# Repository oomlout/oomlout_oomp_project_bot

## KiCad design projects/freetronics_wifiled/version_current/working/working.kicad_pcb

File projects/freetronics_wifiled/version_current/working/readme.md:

# WIFILED by freetronics  
This is a harvested standardized copy of a project from github.  
The original project can be found at:  
https://github.com/freetronics/WIFILED  
Please consult that link for additional, details, files, and license information.  
Note: It was auto harvested and if the original repo had more than one board file or anything out of the ordinary the files here are likely not representative.

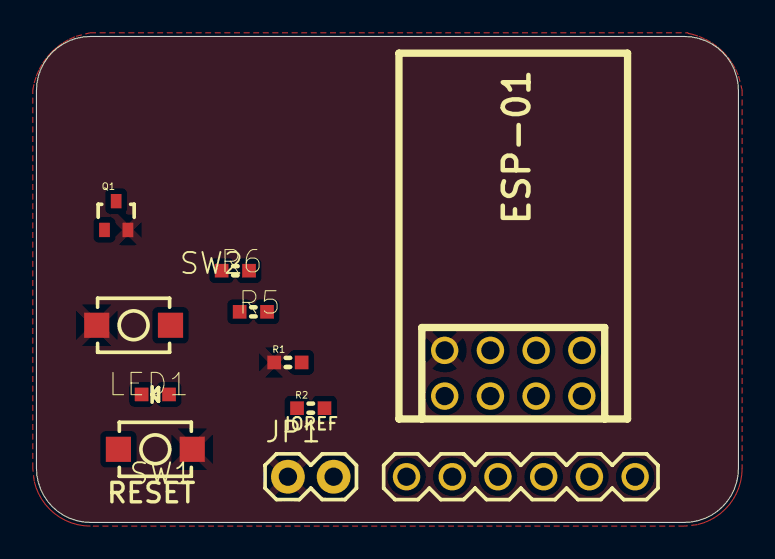
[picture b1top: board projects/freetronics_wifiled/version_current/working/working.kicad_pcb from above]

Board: 2 copper layers, 39.0 x 27.0 mm, 11 parts (0 on the bottom side), 9 nets, no tracks yet.

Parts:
J2: FTDI; 1X06
J9: ESP01
JP1: 1X02
LED1: BLUE; LED-0603
Q1: 2N7002 SOT-323; SOT32-3
R1, R6: 22K; 0603
R2, R5: 1K; 0603
SW1: RESET; TACTILE_SWITCH_SMD_2PIN_TINY
SW2: REFLASH; TACTILE_SWITCH_SMD_2PIN_TINY

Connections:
3.3V: J9.4, JP1.2, R5.2, R6.2
GND: J9.8, JP1.1, Q1.2, R1.1, SW1.1, SW2.2
unnamed: J9.6, SW2.1
unnamed: LED1.C, Q1.3
unnamed: J9.3, SW1.2
unnamed: J9.2, R6.1
unnamed: LED1.A, R5.1
unnamed: Q1.1, R1.2, R2.2
TX: J9.1, R2.1

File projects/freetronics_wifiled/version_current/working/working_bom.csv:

"Id";"Designator";"Footprint";"Quantity";"Designation";"Supplier and ref";
1;"R1,R6";"0603";2;"22K";;;
2;"SW2";"TACTILE_SWITCH_SMD_2PIN_TINY";1;"REFLASH";;;
3;"LED1";"LED-0603";1;"BLUE";;;
4;"J9";"ESP01";1;"ESP01";;;
5;"R2,R5";"0603";2;"1K";;;
6;"J2";"1X06";1;"FTDI";;;
7;"SW1";"TACTILE_SWITCH_SMD_2PIN_TINY";1;"RESET";;;
8;"Q1";"SOT32-3";1;"2N7002 SOT-323";;;
9;"JP1";"1X02";1;"";;;

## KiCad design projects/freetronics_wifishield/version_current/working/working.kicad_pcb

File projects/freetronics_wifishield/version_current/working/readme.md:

# WiFiShield by freetronics  
This is a harvested standardized copy of a project from github.  
The original project can be found at:  
https://github.com/freetronics/WiFiShield  
Please consult that link for additional, details, files, and license information.  
Note: It was auto harvested and if the original repo had more than one board file or anything out of the ordinary the files here are likely not representative.

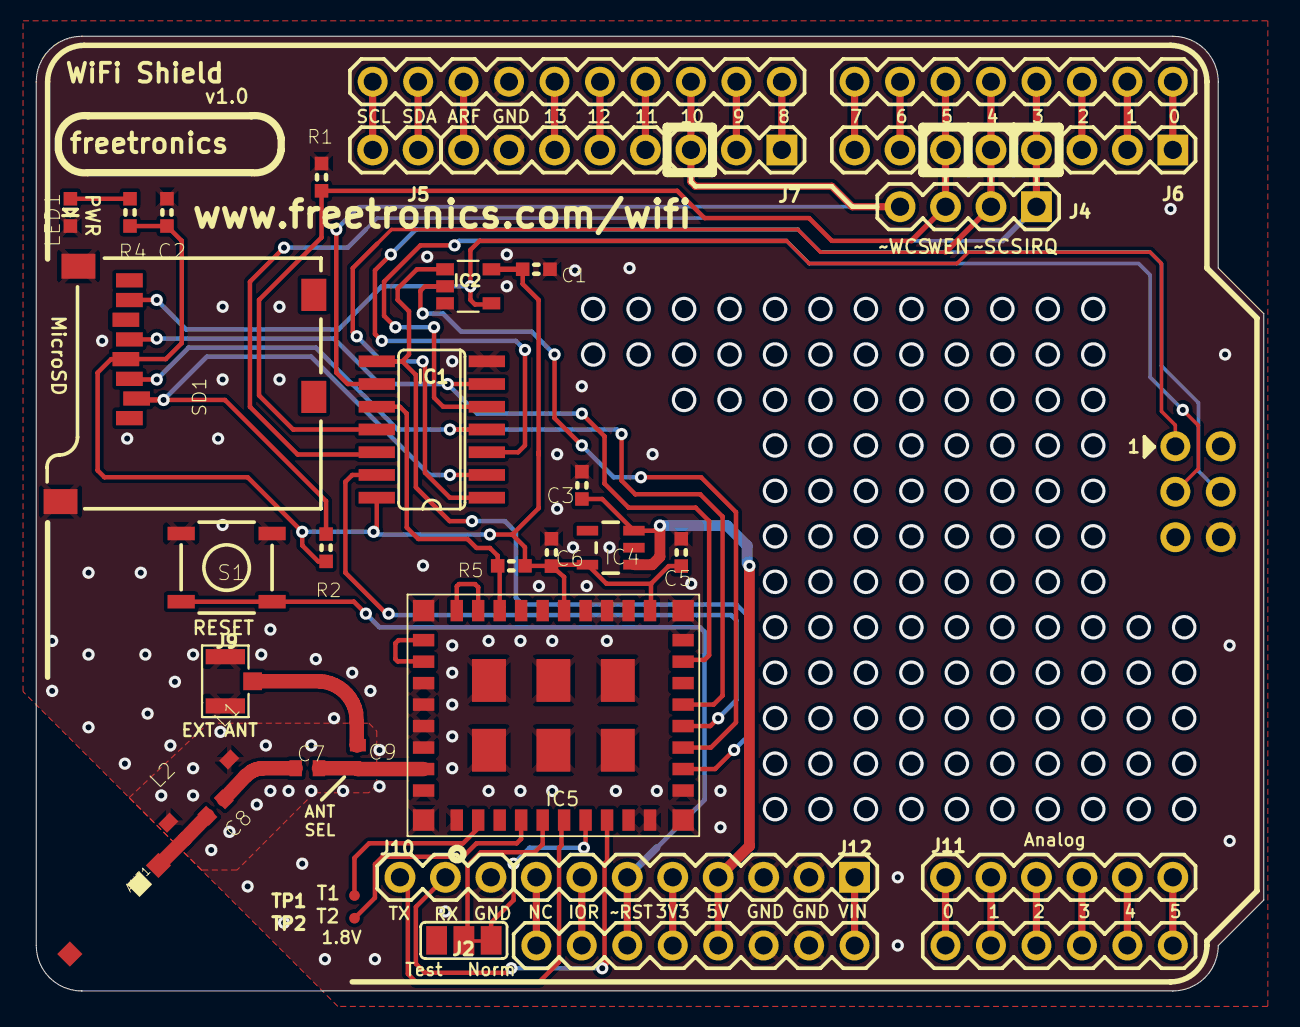
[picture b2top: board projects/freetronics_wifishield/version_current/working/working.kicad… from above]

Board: 2 copper layers, 68.6 x 53.3 mm, 34 parts (0 on the bottom side), 58 nets.

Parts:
ANT1: 2500AT44M0400
C1, C2, C3: 100nF; 0603
C5, C6: 1uF; 0603
C7: 10pF; C0402
C8: 2.2pF; C0402
C9: NP; C0402
IC1: MC74VHCT50A; SO14
IC2: 74AHC1G125; SOT23-5
IC4: AP2112K-3.3; SOT23-5
IC5: CC3000MOD; CC3000
J2: Mode; SJ_2
J4: 1X04
J5: 1X02
J6, J7, J12: 1X08
J8: ARDUINO-SHIELD_R3; ARDUINO-SHIELD_R3_NOHOLES
J9: U.FL-R-SMT-1(10); UFL
J10: Test; 1X03
J11: 1X06
L1: 2.2nH; C0402
L2: NP; C0402
LED1: Power; LED-0603
R1, R2, R5: 10k; 0603
R4: 1k; 0603
S1: Reset; TACTILE_SWITCH_SMD
SD1: USD-SOCKETNEW; MICRO-SD-SOCKET-PP
TP1: R1; TP06R
TP2: R2; TP06R

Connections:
+3V3: C1.2, C2.1, C5.1, C6.2, IC1.14, IC2.5, IC4.5, IC5.19, IC5.23, R2.1, R4.2, R5.1, SD1.4
+5V: C3.2, IC4.1, IC4.3, J8.+5V, J12.4
A0: J8.A0, J11.1
CC3000_EN_3V3: IC1.10, IC5.26, R5.2
CC3000_EN_5V: IC1.11, J4.3, R1.1
CC3000_IRQ_5V: IC1.12, J4.1
CC3000_MISO: IC2.2, IC5.13
GND: C1.1, C2.2, C3.1, C5.2, C6.1, IC1.7, IC2.3, IC4.2, IC5.1, IC5.9, IC5.10, IC5.11, IC5.16, IC5.18, IC5.20, IC5.21, IC5.22, IC5.25, IC5.31, IC5.32, IC5.33, IC5.34, IC5.36, IC5.37, IC5.38, IC5.39, IC5.40, IC5.41, IC5.42, IC5.43, IC5.44, IC5.45, IC5.46, J2.1, J7.7, J8.GND, J8.GND@0, J8.GND@1, J8.GND@2, J9.GND, J9.GND@1, J10.3, J12.2, J12.3, L1.2, L2.2, LED1.C, R1.2, S1.1, S1.2, SD1.6, SD1.GND1, SD1.GND2
IOREF: J8.IOREF, J12.7
MISO_TRISTATE: IC2.4, J8.MISO, SD1.7
MOSI_3V3: IC1.4, IC5.15, SD1.3
MOSI_5V: IC1.3, J8.MOSI
unnamed: IC5.27, IC5.28
unnamed: IC5.29, IC5.30
unnamed: LED1.A, R4.1
unnamed: C7.2, C9.2, IC5.35
unnamed: IC5.4, TP2.TP
unnamed: IC5.2, TP1.TP
unnamed: C9.1, J9.SIG
unnamed: IC1.13, IC5.14
unnamed: J8.A1, J11.2
unnamed: J8.A2, J11.3
unnamed: J8.A3, J11.4
unnamed: J8.A4, J11.5
unnamed: J8.A5, J11.6
unnamed: J8.RESERVED, J12.8
unnamed: J8.VIN, J12.1
unnamed: J8.3V3, J12.5
unnamed: J8.!RESET, J12.6, S1.3, S1.4
unnamed: J6.1, J8.D0
unnamed: J6.2, J8.D1
unnamed: J6.3, J8.D2
unnamed: J6.4, J8.D3
unnamed: J6.5, J8.D4
unnamed: C7.1, C8.2, L1.1
unnamed: ANT1.P$1, C8.1, L2.1
unnamed: J6.6, J8.D5
unnamed: J6.7, J8.D6
unnamed: J6.8, J8.D7
unnamed: J5.1, J8.SDA
unnamed: J7.8, J8.AREF
unnamed: J7.6, J8.D13
unnamed: J7.5, J8.D12
unnamed: J5.2, J8.SCL
unnamed: J7.1, J8.D8
unnamed: J7.2, J8.D9
unnamed: J7.3, J8.D10
unnamed: J7.4, J8.D11
SCK_3V3: IC1.6, IC5.17, SD1.5
SCK_5V: IC1.5, J8.SCK
WL_EN1: IC5.7, J2.3
WL_EN2: IC5.5, J2.2
WL_UART_RX: IC5.8, J10.2
WL_UART_TX: IC5.6, J10.1
~CC3000_CS_3V3: IC1.8, IC2.1, IC5.12
~CC3000_CS_5V: IC1.9, J4.4
~SDCARD_CS_5V: IC1.1, J4.2
~SD_CS_3V3: IC1.2, R2.2, SD1.2

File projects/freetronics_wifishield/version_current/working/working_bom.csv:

"Id";"Designator";"Footprint";"Quantity";"Designation";"Supplier and ref";
1;"J11";"1X06";1;"";;;
2;"L2,C9";"C0402";2;"NP";;;
3;"J12,J6,J7";"1X08";3;"";;;
4;"C3,C2,C1";"0603";3;"100nF";;;
5;"R1,R2,R5";"0603";3;"10k";;;
6;"C5,C6";"0603";2;"1uF";;;
7;"S1";"TACTILE_SWITCH_SMD";1;"Reset";;;
8;"C8";"C0402";1;"2.2pF";;;
9;"J2";"SJ_2";1;"Mode";;;
10;"J10";"1X03";1;"Test";;;
11;"LED1";"LED-0603";1;"Power";;;
12;"J8";"ARDUINO-SHIELD_R3_NOHOLES";1;"ARDUINO-SHIELD_R3";;;
13;"R4";"0603";1;"1k";;;
14;"C7";"C0402";1;"10pF";;;
15;"J5";"1X02";1;"";;;
16;"J4";"1X04";1;"";;;
17;"L1";"C0402";1;"2.2nH";;;
18;"IC4";"SOT23-5";1;"AP2112K-3.3";;;
19;"SD1";"MICRO-SD-SOCKET-PP";1;"USD-SOCKETNEW";;;
20;"TP1";"TP06R";1;"R1";;;
21;"IC1";"SO14";1;"MC74VHCT50A";;;
22;"IC2";"SOT23-5";1;"74AHC1G125";;;
23;"IC5";"CC3000";1;"CC3000MOD";;;
24;"TP2";"TP06R";1;"R2";;;
25;"J9";"UFL";1;"U.FL-R-SMT-1(10)";;;
26;"ANT1";"2500AT44M0400";1;"2500AT44M0400";;;

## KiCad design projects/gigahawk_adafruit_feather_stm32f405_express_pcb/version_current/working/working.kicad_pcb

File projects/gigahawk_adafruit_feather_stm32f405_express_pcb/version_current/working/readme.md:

# Adafruit-Feather-STM32F405-Express-PCB by Gigahawk  
This is a harvested standardized copy of a project from github.  
The original project can be found at:  
https://github.com/Gigahawk/Adafruit-Feather-STM32F405-Express-PCB  
Please consult that link for additional, details, files, and license information.  
Note: It was auto harvested and if the original repo had more than one board file or anything out of the ordinary the files here are likely not representative.

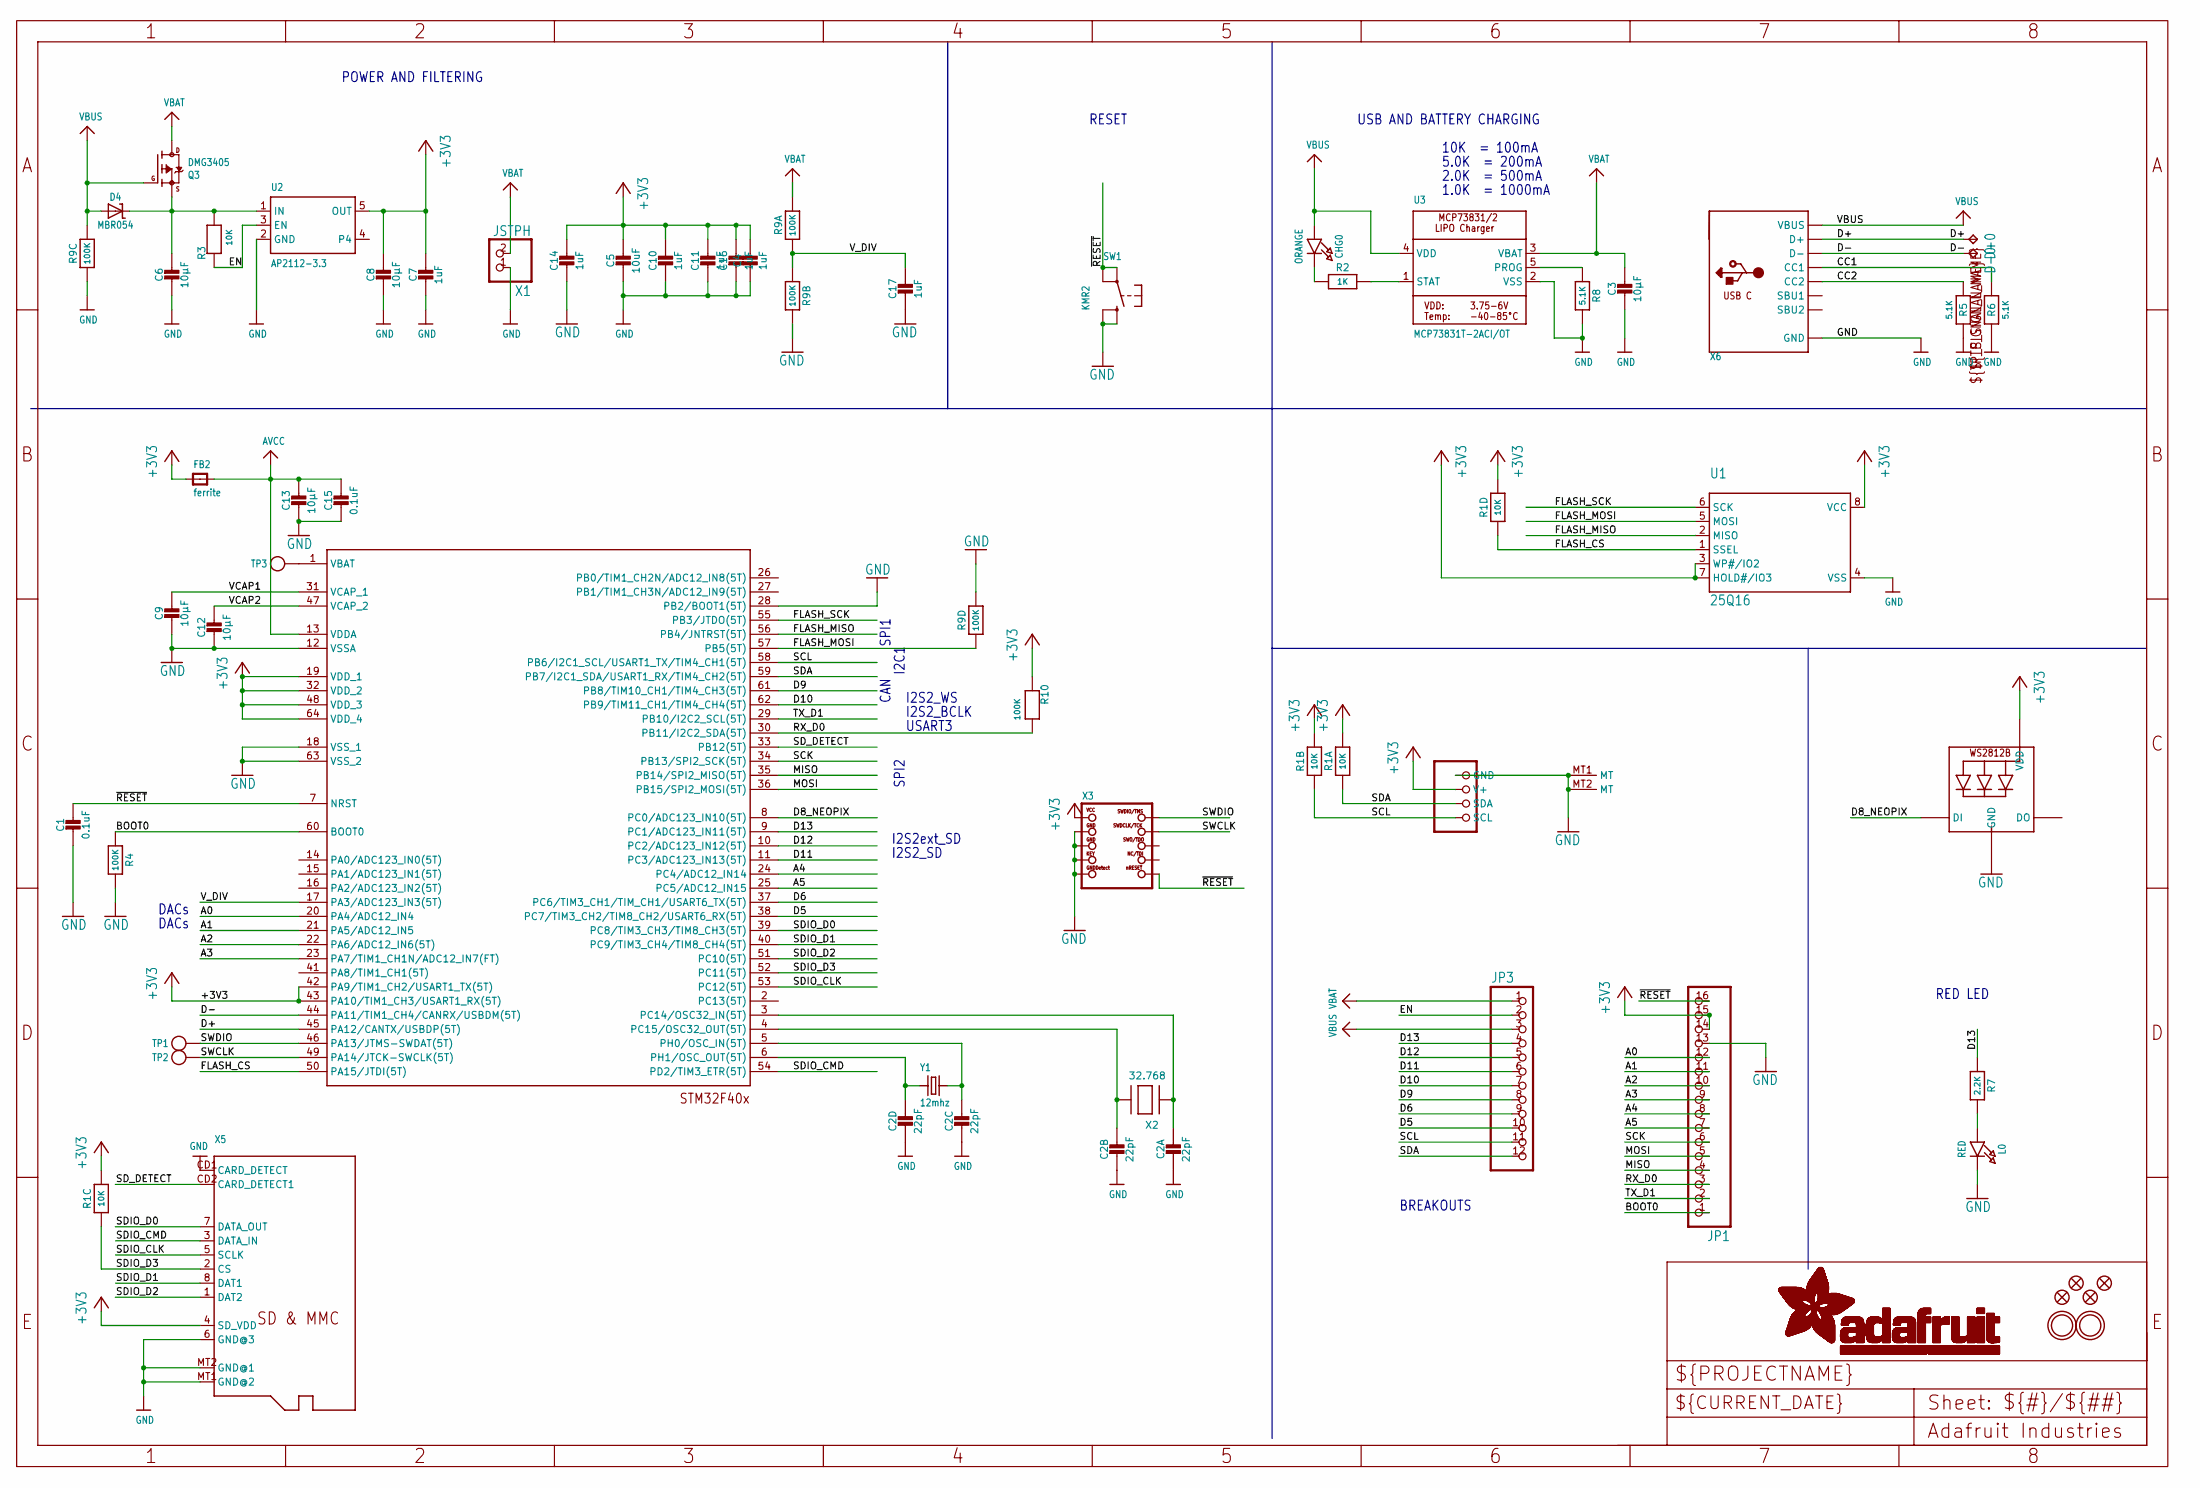
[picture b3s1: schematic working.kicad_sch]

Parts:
C1, C15: 0.1uF; 0603-NO
C2: 22pF; RESPACK_4X0603
C3, C6, C8, C9, C12, C13: 10µF; 0805-NO
C4, C7, C10, C11, C14, C16, C17: 1uF; 0603-NO
C5: 10uF; 0805-NO
CHG0: ORANGE; CHIPLED_0805_NOOUTLINE
CONN1: STEMMA_I2C_QT; JST_SH4
D4: MBR054; SOD-123
D+0: TPB1,27; B1,27
D-0: TPB1,27; B1,27
FB2: ferrite; 0805-NO
JP1: HEADER-1X16ROUND; 1X16_ROUND
JP3: HEADER-1X12; 1X12_ROUND
L0: RED; CHIPLED_0805_NOOUTLINE
LED1: WS2812B3535; LED3535
Q3: DMG3405; SOT23-R
R1: 10K; RESPACK_4X0603_NO
R2: 1K; 0603-NO
R3: 10K; 0603-NO
R4, R10: 100K; 0603-NO
R5, R6, R8: 5.1K; 0603-NO
R7: 2.2K; 0603-NO
R9: 100K; RESPACK_4X0603_NO
SW1: KMR2; BTN_KMR2_4.6X2.8
TP1, TP2, TP3: TESTPOINTROUND1.5MM; TESTPOINT_ROUND_1.5MM
U1: 25Q16; SOIC8_150MIL
U2: AP2112-3.3; SOT23-5
U3: MCP73831T-2ACI/OT; SOT23-5
U$3: STM32F405R; TQFP64
U$5, U$34, U$35, U$37: FIDUCIAL_1MM
U$31, U$32: MOUNTINGHOLE2.5; MOUNTINGHOLE_2.5_PLATED
X1: JSTPH; JSTPH2
X2: 32.768; XTAL3215
X3: JTAG-CORTEX; 2X05_1.27MM_SMT
X5: MICROSD
X6: USB_C; USB_C_CUSB31-CFM2AX-01-X
Y1: 12mhz; CRYSTAL_2.5X2

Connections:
+3V3: C4.1, C5.1, C7.1, C8.1, C10.1, C11.1, C14.1, C16.1, CONN1.2 (V+), FB2.1, JP1.14, JP1.15, LED1.2 (VDD), R1.5 (2), R1.6 (2), R1.7 (2), R1.8 (2), R10.1, U1.3 (WP#/IO2), U1.7 (HOLD#/IO3), U1.8 (VCC), U2.5 (OUT), U$3.19 (VDD_1), U$3.32 (VDD_2), U$3.42 (PA9/TIM1_CH2/USART1_TX(5T)), U$3.43 (PA10/TIM1_CH3/USART1_RX(5T)), U$3.48 (VDD_3), U$3.64 (VDD_4), X3.1 (VCC), X5.4 (SD_VDD)
A0: JP1.12, U$3.20 (PA4/ADC12_IN4)
A1: JP1.11, U$3.21 (PA5/ADC12_IN5)
A2: JP1.10, U$3.22 (PA6/ADC12_IN6(5T))
A3: JP1.9, U$3.23 (PA7/TIM1_CH1N/ADC12_IN7(FT))
A4: JP1.8, U$3.24 (PC4/ADC12_IN14)
A5: JP1.7, U$3.25 (PC5/ADC12_IN15)
AVCC: C13.1, C15.1, FB2.2, U$3.13 (VDDA)
BATTERY: TP3.P$1, U$3.1 (VBAT)
BOOT0: JP1.1, R4.1, U$3.60 (BOOT0)
CC1: R6.2, X6.A5 (CC1)
CC2: R5.2, X6.B5 (CC2)
D5: JP3.10, U$3.38 (PC7/TIM3_CH2/TIM8_CH2/USART6_RX(5T))
D6: JP3.9, U$3.37 (PC6/TIM3_CH1/TIM_CH1/USART6_TX(5T))
D8_NEOPIX: LED1.1 (DI), U$3.8 (PC0/ADC123_IN10(5T))
D9: JP3.8, U$3.61 (PB8/TIM10_CH1/TIM4_CH3(5T))
D10: JP3.7, U$3.62 (PB9/TIM11_CH1/TIM4_CH4(5T))
D11: JP3.6, U$3.11 (PC3/ADC123_IN13(5T))
D12: JP3.5, U$3.10 (PC2/ADC123_IN12(5T))
D13: JP3.4, R7.1, U$3.9 (PC1/ADC123_IN11(5T))
D+: D+0.TP, U$3.45 (PA12/CANTX/USBDP(5T)), X6.A6 (D+), X6.B6 (D+)
D-: D-0.TP, U$3.44 (PA11/TIM1_CH4/CANRX/USBDM(5T)), X6.A7 (D-), X6.B7 (D-)
EN: JP3.2, R3.1, U2.3 (EN)
FLASH_CS: R1.4 (1), U1.1 (SSEL), U$3.50 (PA15/JTDI(5T))
FLASH_MISO: U1.2 (MISO), U$3.56 (PB4/JNTRST(5T))
FLASH_MOSI: R9.4 (1), U1.5 (MOSI), U$3.57 (PB5(5T))
FLASH_SCK: U1.6 (SCK), U$3.55 (PB3/JTDO(5T))
GND: C1.2, C2.5 (2), C2.6 (2), C2.7 (2), C2.8 (2), C3.2, C4.2, C5.2, C6.2, C7.2, C8.2, C9.2, C10.2, C11.2, C12.2, C13.2, C14.2, C15.2, C16.2, C17.2, CONN1.1 (GND), CONN1.MT1 (MT), CONN1.MT2 (MT), JP1.13, L0.C, LED1.4 (GND), R4.2, R5.1, R6.1, R8.2, R9.3 (1), R9.5 (2), R9.7 (2), SW1.B (S), SW1.B' (S1), U1.4 (VSS), U2.2 (GND), U3.2 (VSS), U$3.12 (VSSA), U$3.18 (VSS_1), U$3.28 (PB2/BOOT1(5T)), U$3.63 (VSS_2), X1.1, X3.3 (GND@1), X3.5 (GND@2), X3.7 (KEY), X3.9 (GNDDETECT), X5.6 (GND@3), X5.CD1 (CARD_DETECT), X5.MT1 (GND@2), X5.MT2 (GND@1), X6.A1B12 (GND), X6.B1A12 (GND)
MISO: JP1.4, U$3.35 (PB14/SPI2_MISO(5T))
MOSI: JP1.5, U$3.36 (PB15/SPI2_MOSI(5T))
unnamed: CHG0.C, R2.1
unnamed: L0.A, R7.2
unnamed: R2.2, U3.1 (STAT)
unnamed: R8.1, U3.5 (PROG)
unnamed: C2.4 (1), U$3.3 (PC14/OSC32_IN(5T)), X2.P$1
unnamed: C2.2 (1), U$3.5 (PH0/OSC_IN(5T)), Y1.3 (2)
unnamed: C2.3 (1), U$3.4 (PC15/OSC32_OUT(5T)), X2.P$2
unnamed: C2.1, U$3.6 (PH1/OSC_OUT(5T)), Y1.1
RX_D0: JP1.3, R10.2, U$3.30 (PB11/I2C2_SDA(5T))
SCK: JP1.6, U$3.34 (PB13/SPI2_SCK(5T))
SCL: CONN1.4 (SCL), JP3.11, R1.2 (1), U$3.58 (PB6/I2C1_SCL/USART1_TX/TIM4_CH1(5T))
SDA: CONN1.3 (SDA), JP3.12, R1.1, U$3.59 (PB7/I2C1_SDA/USART1_RX/TIM4_CH2(5T))
SDIO_CLK: U$3.53 (PC12(5T)), X5.5 (SCLK)
SDIO_CMD: U$3.54 (PD2/TIM3_ETR(5T)), X5.3 (DATA_IN)
SDIO_D0: U$3.39 (PC8/TIM3_CH3/TIM8_CH3(5T)), X5.7 (DATA_OUT)
SDIO_D1: U$3.40 (PC9/TIM3_CH4/TIM8_CH4(5T)), X5.8 (DAT1)
SDIO_D2: U$3.51 (PC10(5T)), X5.1 (DAT2)
SDIO_D3: R1.3 (1), U$3.52 (PC11(5T)), X5.2 (CS)
SD_DETECT: U$3.33 (PB12(5T)), X5.CD2 (CARD_DETECT1)
SWCLK: TP2.P$1, U$3.49 (PA14/JTCK-SWCLK(5T)), X3.4 (SWDCLK)
SWDIO: TP1.P$1, U$3.46 (PA13/JTMS-SWDAT(5T)), X3.2 (SWDIO)
TX_D1: JP1.2, U$3.29 (PB10/I2C2_SCL(5T))
VBAT: C3.1, JP3.1, Q3.3 (D), R9.8 (2), U3.3 (VBAT), X1.2
VBUS: CHG0.A, D4.A, JP3.3, Q3.1 (G), R9.6 (2), U3.4 (VDD), X6.A4B9 (VBUS), X6.B4A9 (VBUS)
VCAP1: C9.1, U$3.31 (VCAP_1)
VCAP2: C12.1, U$3.47 (VCAP_2)
VHI: C6.1, D4.C, Q3.2 (S), R3.2, U2.1 (IN)
V_DIV: C17.1, R9.1, R9.2 (1), U$3.17 (PA3/ADC123_IN3(5T))
~RESET: C1.1, JP1.16, SW1.A, SW1.A' (P1), U$3.7 (NRST), X3.10 (NRESET)

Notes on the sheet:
BREAKOUTS
USART3
USB AND BATTERY CHARGING
I2S2_SD
5.0K = 200mA
RED LED
2.0K = 500mA
SPI1
I2S2_WS
10K = 100mA
I2C1
RESET
1.0K = 1000mA
I2S2_BCLK
SPI2
DACs
POWER AND FILTERING
CAN
I2S2ext_SD

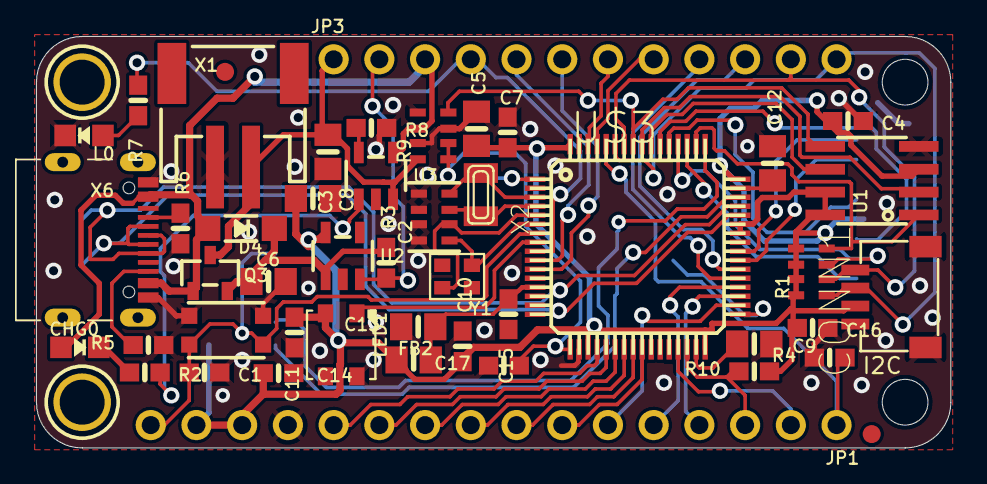
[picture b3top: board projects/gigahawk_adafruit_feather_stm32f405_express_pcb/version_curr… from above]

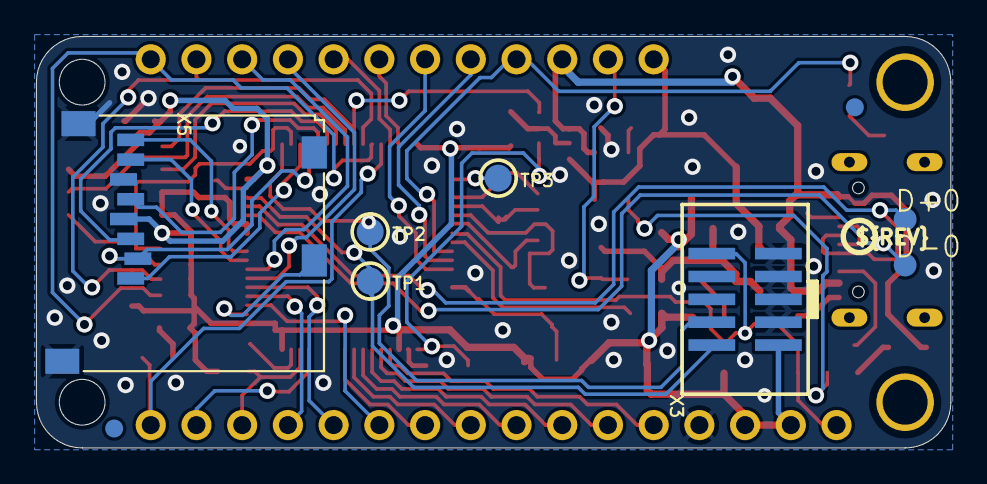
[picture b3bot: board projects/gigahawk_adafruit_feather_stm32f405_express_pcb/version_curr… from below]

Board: 2 copper layers, 50.8 x 22.9 mm, 63 parts (11 on the bottom side), 59 nets.

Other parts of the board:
@HOLE0, @HOLE1: (no value)
U$13: PCBFEAT-REV-040
U$24: FEATHER_STM32F405_TOP
U$40: FEATHER_STM32F405_BOT

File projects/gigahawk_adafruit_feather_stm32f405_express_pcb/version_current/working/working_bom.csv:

Row,Description,Part,References,Value,Footprint,Quantity Per PCB,Status,Datasheet,REV
1,,CAP_4PACK1206,C2,22pF,RESPACK_4X0603,1, ,,
2,,CAP_CERAMIC0603_NO,C1 C15,0.1uF,0603-NO,2, ,,
3,,CAP_CERAMIC0603_NO,C4 C7 C10 C11 C14 C16 C17,1uF,0603-NO,7, ,,
4,,CAP_CERAMIC0805-NOOUTLINE,C3 C5 C6 C8 C9 C12 C13,10µF,0805-NO,7, ,,B
5,,LED0805_NOOUTLINE,CHG0,ORANGE,CHIPLED_0805_NOOUTLINE,1, ,,
6,,STEMMA_I2C_QT,CONN1,STEMMA_I2C_QT,JST_SH4,1, ,,
7,,DIODE-SCHOTTKYSOD-123,D4,MBR054,SOD-123,1, ,,
8,,"TPB1,27",D+0 D-0,"TPB1,27","B1,27",2, ,,
9,,FERRITE-0805NO,FB2,ferrite,0805-NO,1, ,,
10,,HEADER-1X12,JP3,HEADER-1X12,1X12_ROUND,1, ,,
11,,HEADER-1X16ROUND,JP1,HEADER-1X16ROUND,1X16_ROUND,1, ,,
12,,LED0805_NOOUTLINE,L0,RED,CHIPLED_0805_NOOUTLINE,1, ,,
13,,WS2812B3535,LED1,WS2812B3535,LED3535,1, ,,
14,,MOSFET-P,Q3,DMG3405,SOT23-R,1, ,,
15,,RESISTOR_0603_NOOUT,R2,1K,0603-NO,1, ,,
16,,RESISTOR_0603_NOOUT,R7,2.2K,0603-NO,1, ,,
17,,RESISTOR_0603_NOOUT,R5 R6 R8,5.1K,0603-NO,3, ,,
18,,RESISTOR_4PACK_NO,R1,10K,RESPACK_4X0603_NO,1, ,,
19,,RESISTOR_0603_NOOUT,R3,10K,0603-NO,1, ,,
20,,RESISTOR_0603_NOOUT,R4 R10,100K,0603-NO,2, ,,
21,,RESISTOR_4PACK_NO,R9,100K,RESPACK_4X0603_NO,1, ,,
22,,SWITCH_TACT_SMT4.6X2.8,SW1,KMR2,BTN_KMR2_4.6X2.8,1, ,,
23,,SPIFLASH_8PIN,U1,25Q16,SOIC8_150MIL,1, ,,
24,,VREG_SOT23-5,U2,AP2112-3.3,SOT23-5,1, ,,
25,,MCP73831/2,U3,MCP73831T-2ACI/OT,SOT23-5,1, ,,
26,,STM32F405R,U$3,STM32F405R,TQFP64,1, ,,
27,,XTAL-3.2X1.5,X2,32.768,XTAL3215,1, ,,
28,,CON_JST_PH_2PIN,X1,JSTPH,JSTPH2,1, ,,
29,,JTAG-CORTEX,X3,JTAG-CORTEX,2X05_1.27MM_SMT,1, ,,
30,,MICROSD,X5,MICROSD,MICROSD,1, ,,
31,,USB_C,X6,USB_C,USB_C_CUSB31-CFM2AX-01-X,1, ,,
32,,CRYSTAL2.5X2.0,Y1,12mhz,CRYSTAL_2.5X2,1, ,,





Project info:
Schematic:,working
Variant:,default
Revision:,
Date:,2023-08-03_17-21-23
KiCad Version:,7.0.6-7.0.6~ubuntu22.04.1
Statistics:
Component Groups:,32
Component Count:,49 (0 SMD/ 0 THT)
Fitted Components:,49 (0 SMD/ 0 THT)
Number of PCBs:,1
Total Components:,49

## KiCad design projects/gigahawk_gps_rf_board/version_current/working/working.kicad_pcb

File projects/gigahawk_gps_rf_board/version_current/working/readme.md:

# gps-rf-board by Gigahawk  
This is a harvested standardized copy of a project from github.  
The original project can be found at:  
https://github.com/Gigahawk/gps-rf-board  
Please consult that link for additional, details, files, and license information.  
Note: It was auto harvested and if the original repo had more than one board file or anything out of the ordinary the files here are likely not representative.

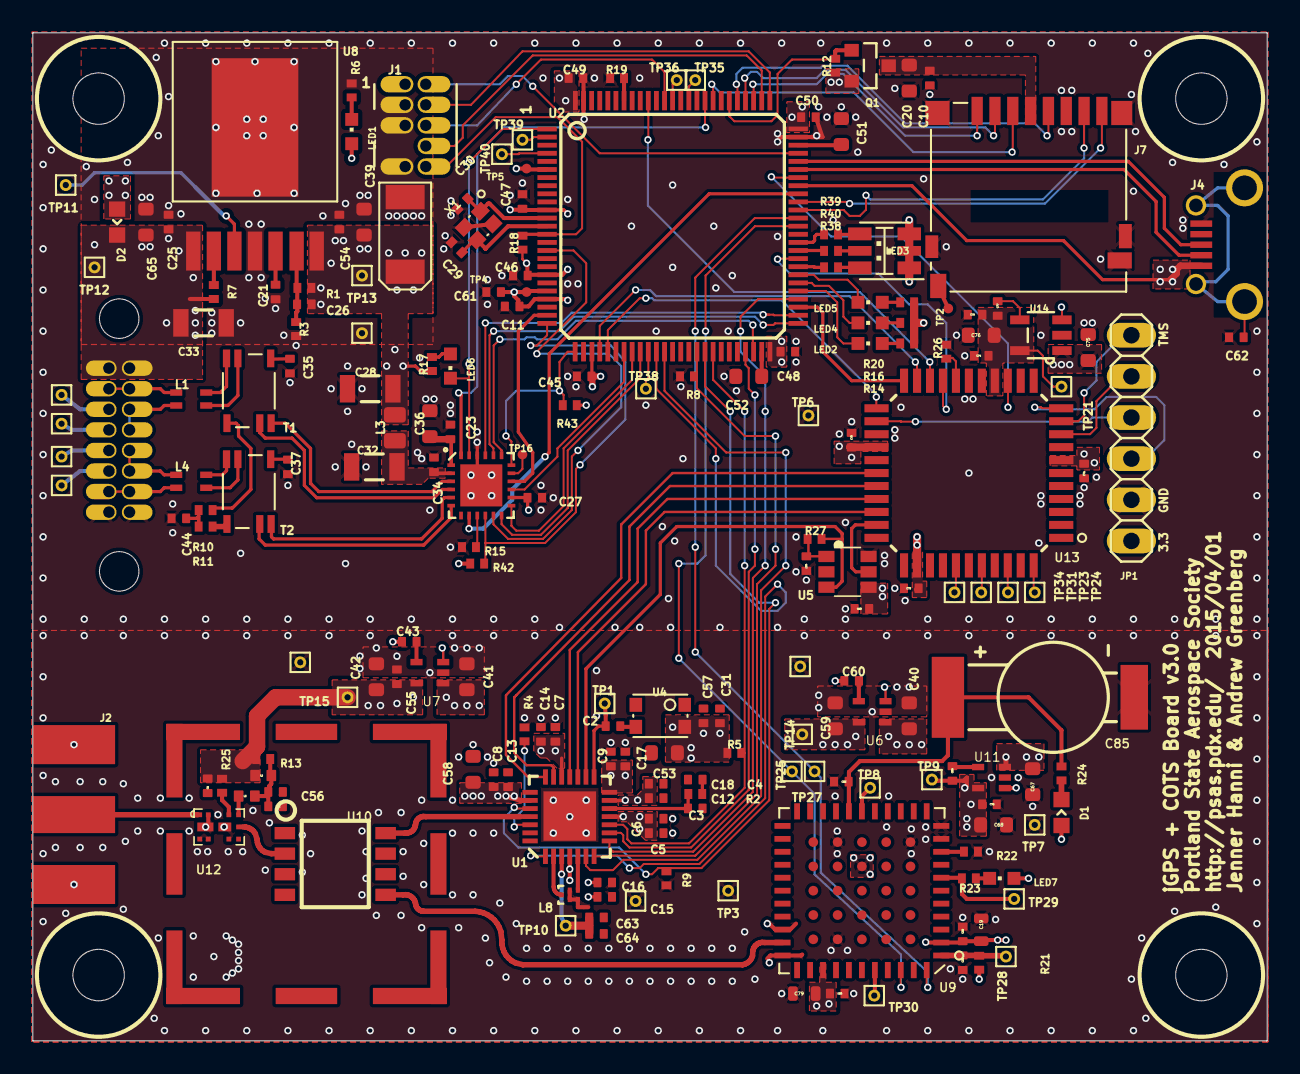
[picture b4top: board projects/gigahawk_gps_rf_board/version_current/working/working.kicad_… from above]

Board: 4 copper layers, 76.2 x 62.2 mm, 199 parts (0 on the bottom side), 150 nets.

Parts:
C1: 330p; .0402-C-NOSILK
C2, C43, C60, C69: 10n; .0402-C-NOSILK
C3: 27p; .0402-C-NOSILK
C4: 470p; .0402-C-NOSILK
C5, C7, C9, C10, C11, C13, C15, C18, C21, C23, C24, C27, C31, C34, C35, C37, C45, C46, C47, C48, C49, C50, C54, C55, C56, C61, C64, C70, C71, C72, C73, C74, C77, C78, C82, C83, C84: 100n; .0402-C-NOSILK
C6, C8, C12, C14, C16, C17, C22, C57, C63, C80: 100p; .0402-C-NOSILK
C19, C79: 1u; .0603-C-NOSILK
C20, C36, C51, C52, C53, C58, C76: 2.2u; .0603-B-NOSILK
C25: 100n 50V; .0402-C-NOSILK
C26: 22n; .0402-C-NOSILK
C28, C32: 22u; 1206-C
C29, C30: 10p; .0402-C-NOSILK
C33: 10u 50V; 1206-C
C38: 100u; EIA6032
C39, C40, C41, C42, C59, C67, C68, C75: 1u; .0603-B-NOSILK
C44, C62: 1n 2kv; .0402-C-NOSILK
C65: 1u 50V; .0603-B-NOSILK
C81: 47p; .0402-C-NOSILK
C85: DSK-3R3H334T-HL; CAP-ELNA-DS-SERIES
D1, D2: DIODE-0603; 0603-B-NOSILK-DIODE
J1: 1.27MM-SWD-CONNECTOR; 1.27MM_2X5
J2: CON_SMA-ENDFIRE_EMERSON_EMERSON-142-0701-801; SMA-CON-EMERSON
J3: ROCKETNET-CONNECTOR-16M; ROCKETNET-M-16
J4: ZX62D-B-5P8
J7: CON_HIROSE_DM3D(MICROSD); HIROSE_DM3D(MICRO-SD)
JP1: 1X06
L1, L4: ACM2012; TDK-ACM2012
L2: 22n; .0402-B-NOSILK
L3: HF70ACC201209-T; .0805-C-NOSILK
L5: 1.8n; .0402-B-NOSILK
L8: SF14-1575F5UU19; SAW_1.4X1.1
LED1: GREEN; CHIPLED_0603
LED2, LED4, LED5, LED6, LED7: YLW; CHIPLED_0603
LED3: SMLV56RGB1W1; LED-3528
Q1: NTR4101P; SOT23
R1, R14, R16, R20, R38, R39, R40: 3.32k; 0402-C-NOSILK@1
R2: 20k; 0402-C-NOSILK@1
R3: 1.07k; 0402-C-NOSILK@1
R4, R6, R17, R23, R24, R42, R43: 1k; 0402-C-NOSILK@1
R5, R8, R9, R12, R18, R19, R22, R26, R27: 10k; 0402-C-NOSILK@1
R7: 61.9k; 0402-C-NOSILK@1
R10, R11: 75; 0402-C-NOSILK@1
R13: 10; 0402-C-NOSILK@1
R15: 6.49k; 0402-C-NOSILK@1
R21: 33k; 0402-C-NOSILK@1
R25: 4.7k; 0402-C-NOSILK@1
SH1: BMI-S-202-SHIELD; BMI-S-202
T1, T2: ALT4532; TDK-ALT4532
TP1, TP3, TP6, TP7, TP8, TP9, TP10, TP11, TP12, TP13, TP14, TP15, TP17, TP18, TP19, TP20, TP21, TP22, TP23, TP24, TP25, TP26, TP27, TP28, TP29, TP30, TP31, TP32, TP33, TP34, TP35, TP36, TP38, TP39, TP40: TEST-POINT15MIL-TEST-POINT; 15MIL-TEST-POINT
TP2, TP4, TP5, TP16: TP06R
U1: MAX2769ETI+; 90-0023
U2: STM32F407VG; LQFP100
U3: KSZ8081; QFN-24
U4: 7Q-16.368MBG-T; TCX_7Q
U5: LT1719S6; SOT23-6
U6, U7, U11: MAX8510EXK29+T; SC70
U8: LMZ12001TZ-ADJ/NOPB; TO-PMOD-7
U9: VENUS838FLPX-L; VENUS638FLPX
U10: BP2G+; MINICIRCUITS
U12: ALM-GP003; AVAGO+SAW+LNA
U13: XC2C64A-5VQG44C; VQ44
U14: MIC5319-1.8V; SOT-23-5
U$1, U$12, U$14, U$18: #4-BARE_MOUNTING_HOLE/.300; #4_.300-BARE+STD_NUT_OR_STAR_WASHER
X1: 25 MHz; 8Y

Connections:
1.8V: C74.1, C76.1, C77.1, C78.1, TP21.P$1, U13.15, U14.5
2.85V-S: C19.1, C22.1, C68.1, C69.1, C70.1, C79.1, C80.1, D1.ANODE, LED7.A, R21.2, TP9.P$1, U9.2, U9.36, U9.58, U11.5
2.85VA: C1.1, C5.1, C6.1, C8.1, C12.1, C13.1, C15.1, C16.1, C18.1, C42.1, C43.1, C55.1, C58.1, L2.2, R13.1, R25.1, TP15.P$1, U1.4, U1.11, U1.13, U1.23, U7.5
2.85VD: C7.1, C9.1, C14.1, C17.1, C31.1, C53.1, C57.1, C59.1, C60.1, R5.2, TP14.P$1, U1.14, U1.19, U4.4, U6.5
3.3VD: C11.2, C26.1, C27.2, C28.2, C38.P$1, C39.1, C40.1, C41.1, C45.2, C46.2, C47.2, C48.2, C49.2, C50.2, C54.1, C61.2, C67.1, C71.1, C72.1, C73.1, C75.1, C83.1, J1.VTREF, JP1.1, L3.2, LED1.A, LED3.1, LED3.2, LED3.3, Q1.2, R1.2, R12.2, R14.2, R16.2, R17.2, R18.2, R20.2, R42.1, R43.1, TP4.TP, TP5.TP, TP13.P$1, U2.6, U2.11, U2.19, U2.21, U2.22, U2.28, U2.50, U2.75, U2.100, U3.14, U5.4, U6.1, U6.3, U7.1, U7.3, U8.7, U11.1, U11.3, U13.7, U13.26, U13.35, U14.1, U14.3
AGND: C1.2, C3.2, C4.2, C5.2, C6.2, C8.2, C12.2, C13.2, C15.2, C16.2, C18.2, C31.2, C53.2, C56.2, C57.2, C58.2, C63.2, C64.2, C81.2, J2.GND, J2.GND@1, J2.GND@2, J2.GND@3, L8.2, L8.3, L8.5, SH1.P$1, SH1.P$2, SH1.P$3, SH1.P$4, SH1.P$5, SH1.P$6, SH1.P$7, SH1.P$8, SH1.P$9, SH1.P$10, SH1.P$11, SH1.P$12, U1.BODY, U4.1, U4.2, U9.21, U9.22, U9.24, U9.25, U9.27, U9.28, U9.29, U9.31, U9.33, U9.61, U9.62, U9.65, U9.69, U10.1, U10.3, U10.4, U10.6, U10.7, U12.2, U12.3, U12.4, U12.9, U12.P$1, U12.P$2
ANTBIAS: C63.1, C64.1, TP10.P$1, U1.3
AUX1: J3.A1, TP22.P$1
AUX2: J3.A2, TP26.P$1
AUX3: J3.A3, TP32.P$1
AUX4: J3.A4, TP33.P$1
BOOT0: R19.1, U2.94
CPLD_DEBUG: U2.59, U13.19
CPLD_IN_ONLY: R26.2, U13.18
CPLD_OUT_SPI1_MOSI: U2.91, U13.20
CPLD_OUT_SPI1_NSS: U2.29, U13.21
CPLD_OUT_SPI1_SCK: U2.30, U13.23
CPLD_OUT_SPI_CLK_SRC: U2.53, U13.22
CPLD_RESET: U2.69, U13.14
CPOUT: C3.1, R2.1, U1.12
ETH_CRS_DV: U2.32, U3.15
ETH_DEBUG: LED6.C, U2.1, U3.23
ETH_MCO1_CLK: U2.67, U3.8
ETH_MDC: U2.16, U3.11
ETH_MDINT: R43.2, U2.26, U3.18
ETH_MDIO: R42.2, U2.25, U3.10
ETH_PHY_NRST: U2.84, U3.24
ETH_RMII_REF_CLK: U2.24, U3.16
ETH_RXD0: U2.33, U3.13
ETH_RXD1: U2.34, U3.12
ETH_TXD0: U2.51, U3.20
ETH_TXD1: U2.52, U3.21
ETH_TX_EN: U2.48, U3.19
GND: C7.2, C9.2, C10.1, C11.1, C14.2, C17.2, C19.2, C20.1, C21.2, C22.2, C23.2, C24.1, C25.2, C27.1, C28.1, C29.1, C30.1, C32.1, C33.2, C34.1, C35.1, C36.2, C37.1, C38.P$2, C39.2, C40.2, C41.2, C42.2, C44.1, C45.1, C46.1, C47.1, C48.1, C49.1, C50.1, C51.1, C52.1, C54.2, C55.2, C59.2, C61.1, C62.1, C65.2, C67.2, C68.2, C70.2, C71.2, C72.2, C73.2, C74.2, C75.2, C76.2, C78.2, C79.2, C80.2, C82.1, C83.2, C84.2, C85.-, J1.GND, J1.GND@2, J1.GNDDET, J3.B-@1, J3.B-@2, J4.P5, J7.G1, J7.G2, J7.G3, J7.G4, J7.P6, J7.S0, JP1.2, R3.1, R4.2, R6.1, R8.1, R9.1, R15.1, R19.2, R22.1, R26.1, TP3.P$1, TP6.P$1, TP7.P$1, TP17.P$1, TP18.P$1, TP19.P$1, TP20.P$1, U2.10, U2.20, U2.27, U2.74, U2.99, U3.22, U3.PAD, U5.2, U5.6, U6.2, U7.2, U8.4, U8.EP, U9.10, U9.11, U9.15, U9.19, U9.49, U9.60, U9.64, U11.2, U13.4, U13.17, U13.25, U14.2, X1.2, X1.4
I0: U1.20, U13.29
I1: U1.21, U13.28
LED2: LED2.C, U2.55
LED4: LED4.C, U2.56
LED5: LED5.C, U2.57
LED/GPIO: R23.2, TP29.P$1, U9.7
LNA-POWER-FILTERED: C56.1, C81.1, L2.1, L5.1, R13.2
LNAOUT: L8.1, U1.2
MAX-CLKOUT: U5.5, U13.32
MAX-RF: U1.25, U10.8
MAX_ANTFLAG: U1.1, U2.36
MAX_CFG_SPI2_MOSI: U1.8, U2.54
MAX_CFG_SPI2_SCLK: U1.9, U2.47
MAX_CFG_~CS: R5.1, U1.10, U2.43
MAX_CLK_OUT: R27.2, U1.16, U5.3
MAX_LD: U1.6, U2.37
MAX_~IDLE: R9.2, U1.24, U2.42
MAX_~SHDN: R8.2, U1.7, U2.41
MIXIN: L8.4, U1.5
unnamed: TP11.P$1, U8.3
unnamed: TP16.TP, U3.17
unnamed: JP1.6, U13.10
unnamed: C69.2, U11.4
unnamed: J2.SIG, U12.1
unnamed: C21.1, U8.5
unnamed: C26.2, R1.1, R3.2, U8.6
unnamed: J3.T+@13, J3.T+@14, L1.1
unnamed: TP24.P$1, U13.44
unnamed: R7.2, U8.2
unnamed: TP23.P$1, U13.42
unnamed: LED3.5, R38.1
unnamed: C43.2, U7.4
unnamed: U10.2, U12.6
unnamed: C44.2, R10.1, R11.1
unnamed: C60.2, U6.4
unnamed: R22.2, U9.9
unnamed: LED3.4, R39.1
unnamed: LED1.C, R6.2
unnamed: J3.T-@9, J3.T-@11, L1.2
unnamed: LED7.C, R23.1
unnamed: LED6.A, R17.1
unnamed: C35.2, T1.3
unnamed: J3.R+@5, J3.R+@7, L4.1
unnamed: J3.R-@3, J3.R-@4, L4.2
unnamed: L1.4, T1.1
unnamed: L1.3, T1.2
unnamed: L4.4, T2.1
unnamed: L4.3, T2.2
unnamed: R11.2, T1.6
unnamed: R10.2, T2.6
unnamed: TP31.P$1, U13.40
unnamed: JP1.5, U13.9
unnamed: C4.1, R2.2
unnamed: LED3.6, R40.1
unnamed: J7.S1, TP2.TP
unnamed: D1.CATHODE, R24.2
unnamed: T2.4, U3.5
unnamed: T1.5, U3.4
unnamed: LED2.A, R14.1
unnamed: C84.1, R27.1, U5.1
unnamed: T2.5, U3.6
unnamed: R15.2, U3.9
unnamed: C37.2, T2.3
unnamed: T1.4, U3.3
unnamed: TP34.P$1, U13.38
unnamed: TP35.P$1, U2.86
unnamed: LED4.A, R16.1
unnamed: LED5.A, R20.1
unnamed: JP1.4, U13.24
unnamed: C2.1, U4.3
unnamed: TP36.P$1, U2.88
unnamed: JP1.3, U13.11
unnamed: C77.2, U14.4
unnamed: TP38.P$1, U2.35
unnamed: TP39.P$1, U2.2
unnamed: TP40.P$1, U2.4
unnamed: R25.2, U12.8
unnamed: L5.2, U12.7
OSC_IN: C30.2, U2.12, X1.1
OSC_OUT: C29.2, U2.13, X1.3
PGM: R4.1, U1.26
Q0: U1.18, U13.30
Q1: U1.17, U13.31
RGB-B: R40.2, U2.58
RGB-G: R39.2, U2.61
RGB-R: R38.2, U2.60
RTC: TP8.P$1, U9.17
SD-VDD: C10.2, C20.2, J7.P4, Q1.3
SDIO_CLK: J7.P5, U2.80
SDIO_CMD: J7.P3, U2.83
SDIO_D0: J7.P7, U2.65
SDIO_D1: J7.P8, U2.66
SDIO_D2: J7.P1, U2.78
SDIO_D3: J7.P2, U2.79
SDIO_PWR: Q1.1, R12.1, U2.81
SHLD: C62.2, J4.P$1, J4.P$2, J4.P$3, J4.P$4
STM_USART6_RX: TP27.P$1, U2.64, U9.44
STM_USART6_TX: TP25.P$1, U2.63, U9.42
STQ-PPS: TP30.P$1, U9.40
STQ-RF: U9.32, U10.5
STQ-VBAT: C82.2, C85.+, R24.1, U9.18
STQ-~RST: C24.2, R21.1, TP28.P$1, U9.1
TCK: J1.SWDCLK, U2.76
TDI: J1.NC, U2.77
TDO: J1.SWO, U2.89
TMS: J1.SWDIO, U2.72
USB_FS_DM: J4.P2, U2.70
USB_FS_DP: J4.P3, U2.71
USB_FS_VBUS: D2.ANODE, J4.P1, U2.68
VCAP_1: C52.2, U2.49
VCAP_2: C51.2, U2.73
VDDA_3.3: C32.2, C34.2, L3.1, U3.2
VDD_1.2: C23.1, C36.1, U3.1
VIN: C25.1, C33.1, C65.1, D2.CATHODE, J3.B+@15, J3.B+@16, R7.1, TP12.P$1, U8.1
XTAL: C2.2, TP1.P$1, U1.15
~RST: J1.!RESET, R18.1, U2.14

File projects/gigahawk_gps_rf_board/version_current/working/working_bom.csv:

"Id";"Designator";"Footprint";"Quantity";"Designation";"Supplier and ref";
1;"JP1";"1X06";1;"";;;
2;"TP5,TP2,TP16,TP4";"TP06R";4;"";;;
3;"C73,C54,C78,C24,C18,C72,C11,C9,C48,C7,C74,C35,C23,C15,C56,C21,C71,C83,C84,C46,C31,C61,C45,C47,C82,C37,C50,C13,C34,C64,C5,C55,C77,C49,C70,C27,C10";".0402-C-NOSILK";37;"100n";;;
4;"TP10,TP22,TP33,TP12,TP11,TP31,TP28,TP29,TP20,TP39,TP17,TP40,TP23,TP15,TP7,TP13,TP25,TP35,TP8,TP30,TP18,TP34,TP32,TP1,TP26,TP3,TP21,TP38,TP27,TP36,TP14,TP24,TP19,TP9,TP6";"15MIL-TEST-POINT";35;"TEST-POINT15MIL-TEST-POINT";;;
5;"C26";".0402-C-NOSILK";1;"22n";;;
6;"U13";"VQ44";1;"XC2C64A-5VQG44C";;;
7;"U6,U7,U11";"SC70";3;"MAX8510EXK29+T";;;
8;"C6,C57,C14,C17,C16,C22,C63,C80,C8,C12";".0402-C-NOSILK";10;"100p";;;
9;"R15";"0402-C-NOSILK@1";1;"6.49k";;;
10;"X1";"8Y";1;"25 MHz";;;
11;"U$1,U$14,U$18,U$12";"#4_.300-BARE+STD_NUT_OR_STAR_WASHER";4;"#4-BARE_MOUNTING_HOLE/.300";;;
12;"C32,C28";"1206-C";2;"22u";;;
13;"C65";".0603-B-NOSILK";1;"1u 50V";;;
14;"T1,T2";"TDK-ALT4532";2;"ALT4532";;;
15;"R17,R4,R42,R43,R23,R6,R24";"0402-C-NOSILK@1";7;"1k";;;
16;"C53,C20,C58,C36,C51,C76,C52";".0603-B-NOSILK";7;"2.2u";;;
17;"U8";"TO-PMOD-7";1;"LMZ12001TZ-ADJ/NOPB";;;
18;"U5";"SOT23-6";1;"LT1719S6";;;
19;"C79,C19";".0603-C-NOSILK";2;"1u";;;
20;"R7";"0402-C-NOSILK@1";1;"61.9k";;;
21;"L3";".0805-C-NOSILK";1;"HF70ACC201209-T";;;
22;"C39,C42,C67,C40,C59,C68,C41,C75";".0603-B-NOSILK";8;"1u";;;
23;"J2";"SMA-CON-EMERSON";1;"CON_SMA-ENDFIRE_EMERSON_EMERSON-142-0701-801";;;
24;"C2,C60,C69,C43";".0402-C-NOSILK";4;"10n";;;
25;"C33";"1206-C";1;"10u 50V";;;
26;"R8,R12,R22,R9,R18,R27,R26,R5,R19";"0402-C-NOSILK@1";9;"10k";;;
27;"LED7,LED2,LED6,LED5,LED4";"CHIPLED_0603";5;"YLW";;;
28;"C62,C44";".0402-C-NOSILK";2;"1n 2kv";;;
29;"J4";"ZX62D-B-5P8";1;"ZX62D-B-5P8";;;
30;"R14,R40,R1,R16,R39,R38,R20";"0402-C-NOSILK@1";7;"3.32k";;;
31;"U9";"VENUS638FLPX";1;"VENUS838FLPX-L";;;
32;"R2";"0402-C-NOSILK@1";1;"20k";;;
33;"U1";"90-0023";1;"MAX2769ETI+";;;
34;"C29,C30";".0402-C-NOSILK";2;"10p";;;
35;"U12";"AVAGO+SAW+LNA";1;"ALM-GP003";;;
36;"C38";"EIA6032";1;"100u";;;
37;"R25";"0402-C-NOSILK@1";1;"4.7k";;;
38;"J7";"HIROSE_DM3D(MICRO-SD)";1;"CON_HIROSE_DM3D(MICROSD)";;;
39;"C4";".0402-C-NOSILK";1;"470p";;;
40;"SH1";"BMI-S-202";1;"BMI-S-202-SHIELD";;;
41;"R10,R11";"0402-C-NOSILK@1";2;"75";;;
42;"C1";".0402-C-NOSILK";1;"330p";;;
43;"J3";"ROCKETNET-M-16";1;"ROCKETNET-CONNECTOR-16M";;;
44;"D2,D1";"0603-B-NOSILK-DIODE";2;"DIODE-0603";;;
45;"J1";"1.27MM_2X5";1;"1.27MM-SWD-CONNECTOR";;;
46;"U10";"MINICIRCUITS";1;"BP2G+";;;
47;"Q1";"SOT23";1;"NTR4101P";;;
48;"R13";"0402-C-NOSILK@1";1;"10";;;
49;"C81";".0402-C-NOSILK";1;"47p";;;
50;"L2";".0402-B-NOSILK";1;"22n";;;
51;"L5";".0402-B-NOSILK";1;"1.8n";;;
52;"U3";"QFN-24";1;"KSZ8081";;;
53;"L4,L1";"TDK-ACM2012";2;"ACM2012";;;
54;"U14";"SOT-23-5";1;"MIC5319-1.8V";;;
55;"LED1";"CHIPLED_0603";1;"GREEN";;;
56;"C85";"CAP-ELNA-DS-SERIES";1;"DSK-3R3H334T-HL";;;
57;"C25";".0402-C-NOSILK";1;"100n 50V";;;
58;"U2";"LQFP100";1;"STM32F407VG";;;
59;"R21";"0402-C-NOSILK@1";1;"33k";;;
60;"U4";"TCX_7Q";1;"7Q-16.368MBG-T";;;
61;"C3";".0402-C-NOSILK";1;"27p";;;
62;"R3";"0402-C-NOSILK@1";1;"1.07k";;;
63;"L8";"SAW_1.4X1.1";1;"SF14-1575F5UU19";;;
64;"LED3";"LED-3528";1;"SMLV56RGB1W1";;;

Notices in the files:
projects/freetronics_wifiled/version_current/working/working.kicad_sch:
Copyright 2018 SuperHouse Automation Pty Ltd
Released under the terms of
the TAPR Open Hardware License
projects/freetronics_wifishield/version_current/working/working.kicad_pcb:
(C) 2014 Freetronics Pty Ltd
Licensed under TAPR
projects/gigahawk_kmk_firmware/version_current/working/working.kicad_sch:
https://creativecommons.org/licenses/by-sa/4.0
Released under the Creative Commons
parts and their libraries:
Released under the Creative Commons Attribution Share-Alike 4.0 License
